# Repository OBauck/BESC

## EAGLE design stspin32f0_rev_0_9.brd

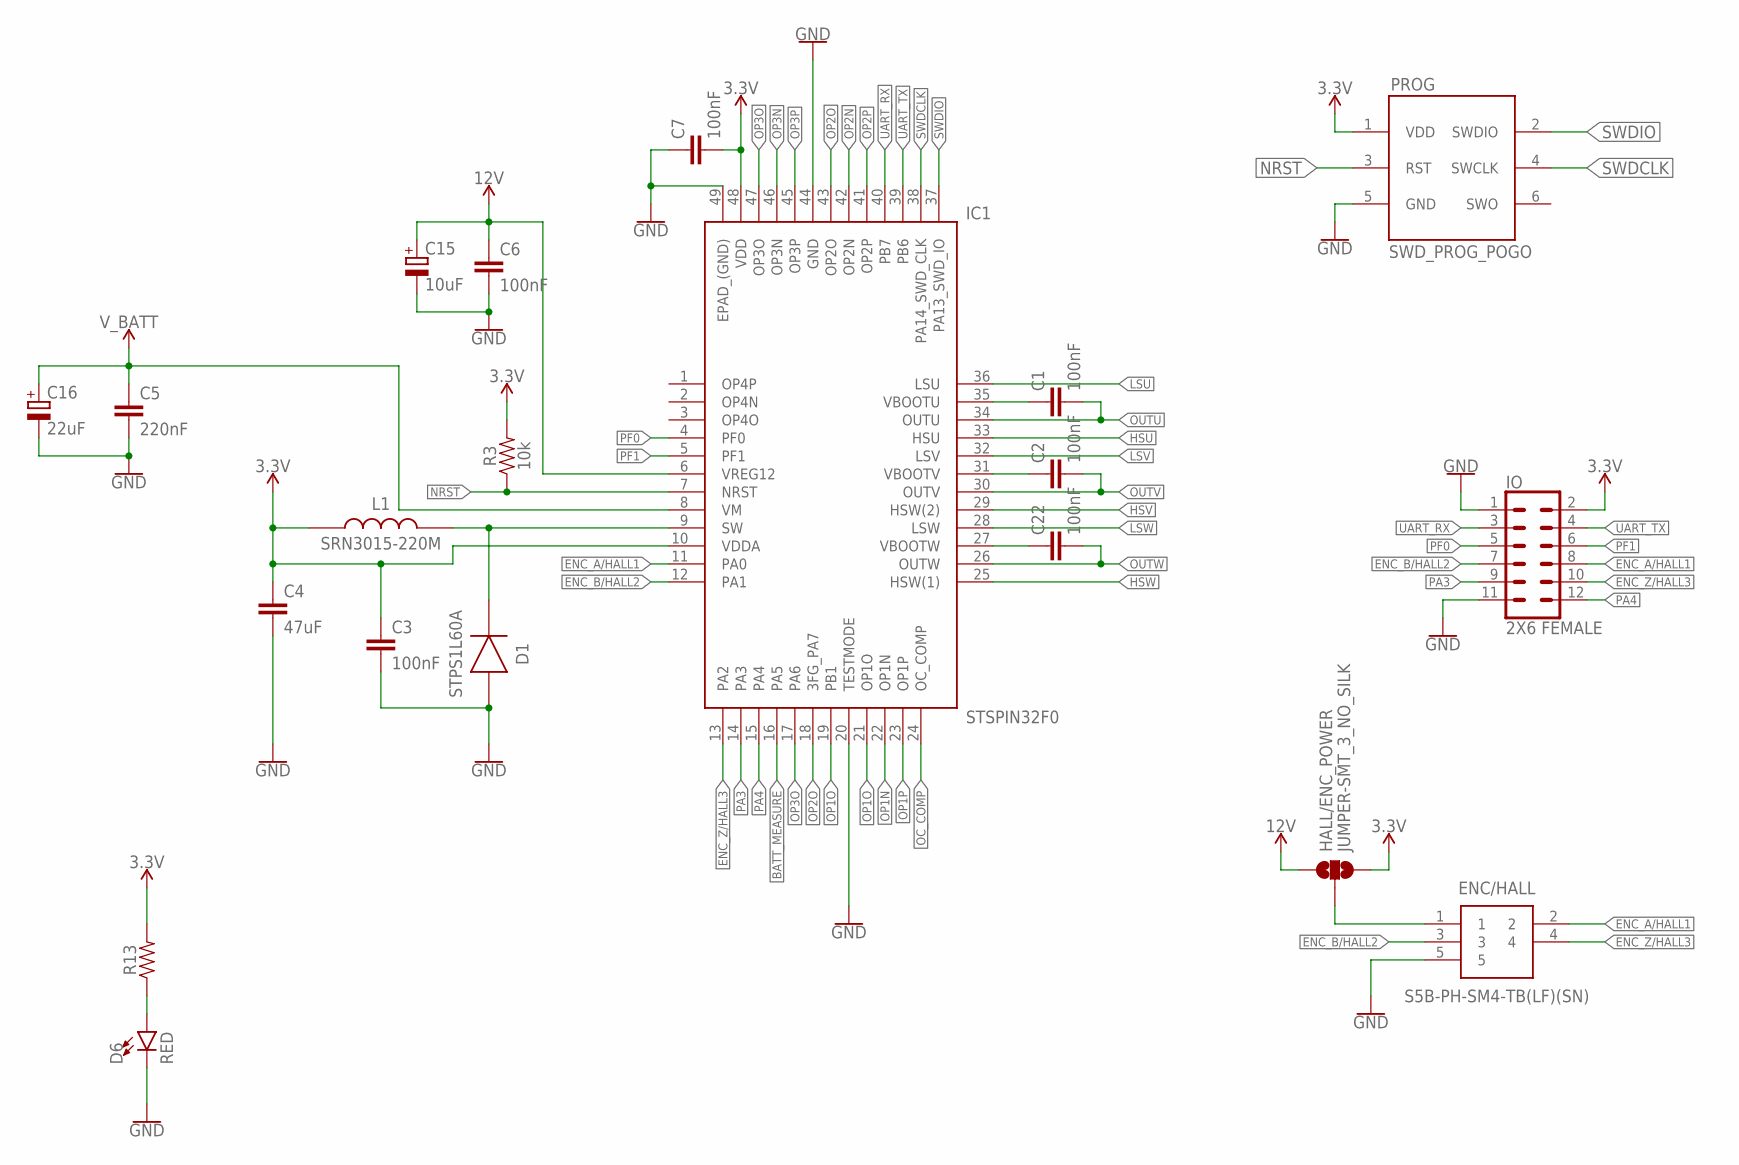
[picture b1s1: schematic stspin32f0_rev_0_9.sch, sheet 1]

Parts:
C1, C2, C3, C6, C7, C22: 100nF; 0603
C4: 47uF; 0805
C5: 220nF; 0805
C15: 10uF; UD-5X5,8_NICHICON
C16: 22uF; UD-6,3X5,8_NICHICON
D1: STPS1L60A; DIOM5126X265N
D6: RED; LED-0603
ENC/HALL: S5B-PH-SM4-TB(LF)(SN); S5B-PH-SM4-TB_1
HALL/ENC_POWER: JUMPER-SMT_3_NO_SILK; SMT-JUMPER_3_NO_SILK
IC1: STSPIN32F0; QFN50P700X700X100-49N
IO: 2X6 FEMALE; 2X6
L1: SRN3015-220M; SRN3015
PROG: SWD_PROG_POGO; 1X06_1.27MM
R3: 10k; 0603
R13: RES-1/10W-5%-0603; 0603

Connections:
3.3V: C3.1, C4.1, C7.2, HALL/ENC_POWER.3, IC1.10 (VDDA), IC1.48 (VDD), IO.2, L1.1, PROG.1 (VDD), R3.2, R13.2; also elsewhere on the board
12V: C6.1, C15.+, HALL/ENC_POWER.1, IC1.6 (VREG12)
BATT_MEASURE: IC1.16 (PA5); also elsewhere on the board
ENC_A/HALL1: ENC/HALL.2, IC1.11 (PA0), IO.8
ENC_B/HALL2: ENC/HALL.3, IC1.12 (PA1), IO.7
ENC_Z/HALL3: ENC/HALL.4, IC1.13 (PA2), IO.10
GND: C3.2, C4.2, C5.2, C6.2, C7.1, C15.-, C16.-, D1.2 (A), D6.C, ENC/HALL.5, IC1.20 (TESTMODE), IC1.44 (GND), IC1.49 (EPAD_(GND)), IO.1, IO.11, PROG.5 (GND); also elsewhere on the board
HSU: IC1.33 (HSU); also elsewhere on the board
HSV: IC1.29 (HSW(2)); also elsewhere on the board
HSW: IC1.25 (HSW(1)); also elsewhere on the board
LSU: IC1.36 (LSU); also elsewhere on the board
LSV: IC1.32 (LSV); also elsewhere on the board
LSW: IC1.28 (LSW); also elsewhere on the board
unnamed: C1.1, IC1.35 (VBOOTU)
unnamed: D1.1 (K), IC1.9 (SW), L1.2
unnamed: D6.A, R13.1
unnamed: C2.1, IC1.31 (VBOOTV)
unnamed: C22.1, IC1.27 (VBOOTW)
unnamed: ENC/HALL.1, HALL/ENC_POWER.2
NRST: IC1.7 (NRST), PROG.3 (RST), R3.1
OC_COMP: IC1.24 (OC_COMP); also elsewhere on the board
OP1N: IC1.22 (OP1N); also elsewhere on the board
OP1O: IC1.19 (PB1), IC1.21 (OP1O); also elsewhere on the board
OP1P: IC1.23 (OP1P); also elsewhere on the board
OP2N: IC1.42 (OP2N); also elsewhere on the board
OP2O: IC1.18 (3FG_PA7), IC1.43 (OP2O); also elsewhere on the board
OP2P: IC1.41 (OP2P); also elsewhere on the board
OP3N: IC1.46 (OP3N); also elsewhere on the board
OP3O: IC1.17 (PA6), IC1.47 (OP3O); also elsewhere on the board
OP3P: IC1.45 (OP3P); also elsewhere on the board
OUTU: C1.2, IC1.34 (OUTU); also elsewhere on the board
OUTV: C2.2, IC1.30 (OUTV); also elsewhere on the board
OUTW: C22.2, IC1.26 (OUTW); also elsewhere on the board
PA3: IC1.14 (PA3), IO.9
PA4: IC1.15 (PA4), IO.12
PF0: IC1.4 (PF0), IO.5
PF1: IC1.5 (PF1), IO.6
SWDCLK: IC1.38 (PA14_SWD_CLK), PROG.4 (SWCLK)
SWDIO: IC1.37 (PA13_SWD_IO), PROG.2 (SWDIO)
UART_RX: IC1.40 (PB7), IO.3
UART_TX: IC1.39 (PB6), IO.4
V_BATT: C5.1, C16.+, IC1.8 (VM); also elsewhere on the board

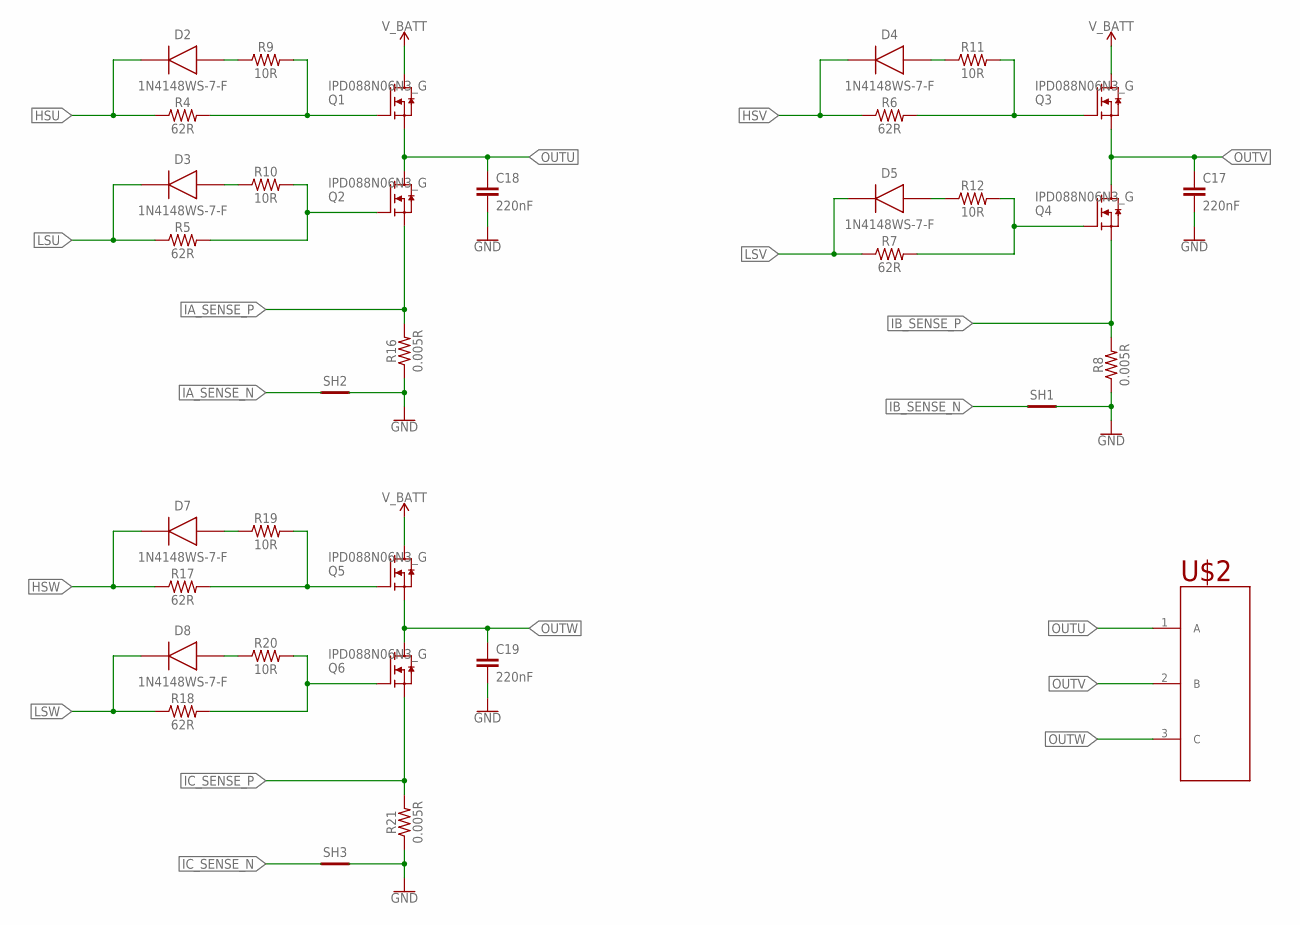
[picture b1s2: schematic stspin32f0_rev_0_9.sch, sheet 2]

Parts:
C17, C18, C19: 220nF; 0805
D2, D3, D4, D5, D7, D8: 1N4148WS-7-F; SOD2513X120N
Q1, Q2, Q3, Q4, Q5, Q6: IPD088N06N3_G; DPAK(TO-252-3)
R4, R5, R6, R7, R17, R18: 62R; 0603
R8, R16, R21: 0.005R; R2512
R9, R10, R11, R12, R19, R20: 10R; 0603
SH1, SH2, SH3: SHORTT5; SHORT_TOP-50
U$2: MR30; MR30PW

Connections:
GND: C17.2, C18.2, C19.2, R8.1, R16.1, R21.1, SH1.2, SH2.2, SH3.2; also elsewhere on the board
HSU: D2.1 (K), R4.1; also elsewhere on the board
HSV: D4.1 (K), R6.1; also elsewhere on the board
HSW: D7.1 (K), R17.1; also elsewhere on the board
IA_SENSE_N: SH2.1; also elsewhere on the board
IA_SENSE_P: Q2.3 (S), R16.2; also elsewhere on the board
IB_SENSE_N: SH1.1; also elsewhere on the board
IB_SENSE_P: Q4.3 (S), R8.2; also elsewhere on the board
IC_SENSE_N: SH3.1; also elsewhere on the board
IC_SENSE_P: Q6.3 (S), R21.2; also elsewhere on the board
LSU: D3.1 (K), R5.1; also elsewhere on the board
LSV: D5.1 (K), R7.1; also elsewhere on the board
LSW: D8.1 (K), R18.1; also elsewhere on the board
unnamed: D7.2 (A), R19.1
unnamed: D8.2 (A), R20.1
unnamed: D4.2 (A), R11.1
unnamed: D2.2 (A), R9.1
unnamed: D3.2 (A), R10.1
unnamed: Q6.1 (G), R18.2, R20.2
unnamed: D5.2 (A), R12.1
unnamed: Q5.1 (G), R17.2, R19.2
unnamed: Q4.1 (G), R7.2, R12.2
unnamed: Q3.1 (G), R6.2, R11.2
unnamed: Q2.1 (G), R5.2, R10.2
unnamed: Q1.1 (G), R4.2, R9.2
OUTU: C18.1, Q1.3 (S), Q2.2 (D), U$2.1 (A); also elsewhere on the board
OUTV: C17.1, Q3.3 (S), Q4.2 (D), U$2.2 (B); also elsewhere on the board
OUTW: C19.1, Q5.3 (S), Q6.2 (D), U$2.3 (C); also elsewhere on the board
V_BATT: Q1.2 (D), Q3.2 (D), Q5.2 (D); also elsewhere on the board

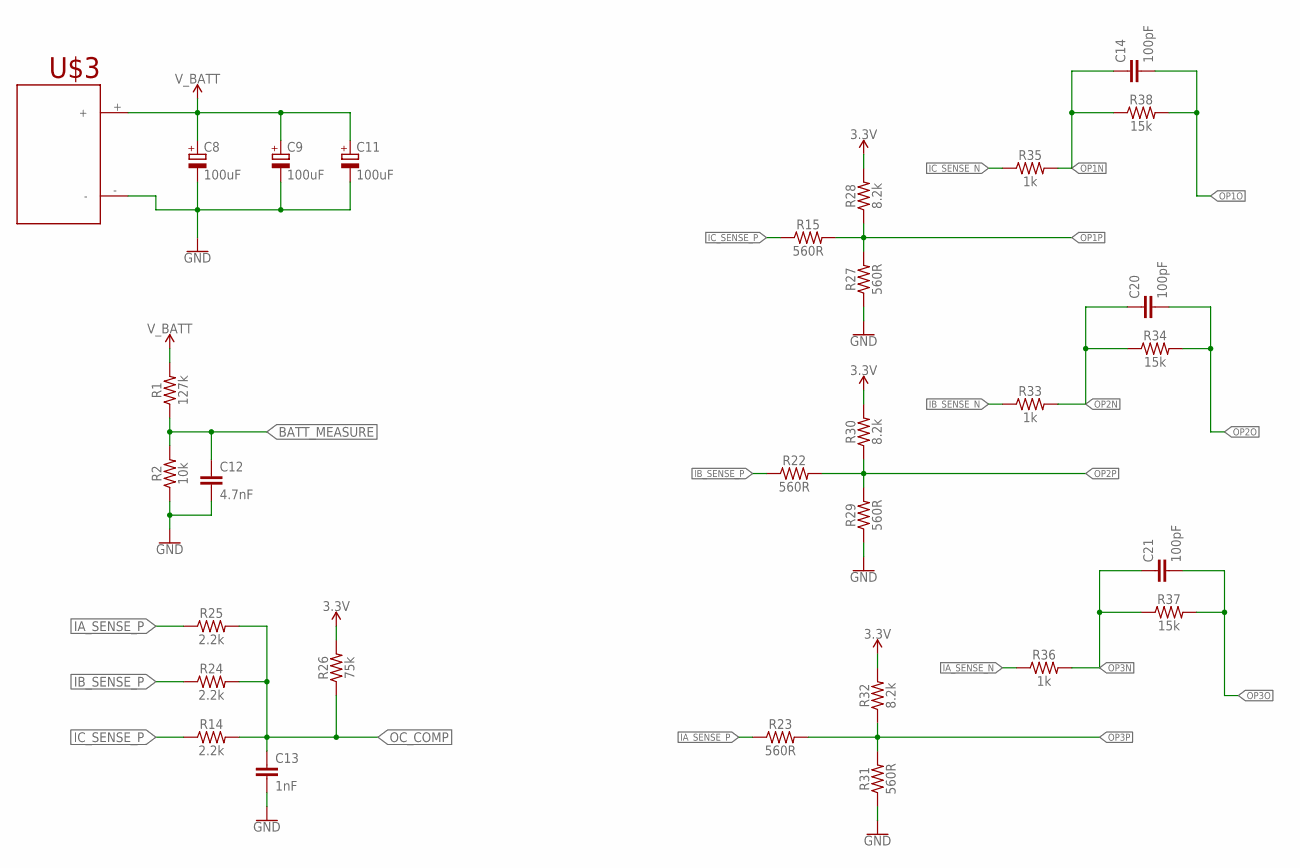
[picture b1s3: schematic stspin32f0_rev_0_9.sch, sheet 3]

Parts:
C8, C9, C11: 100uF; UD-6,3X7,7_NICHICON
C12: 4.7nF; 0603
C13: 1nF; 0603
C14, C20, C21: 100pF; 0603
R1: 127k; 0603
R2: 10k; 0603
R14, R24, R25: 2.2k; 0603
R15, R22, R23, R27, R29, R31: 560R; 0603
R26: 75k; 0603
R28, R30, R32: 8.2k; 0603
R33, R35, R36: 1k; 0603
R34, R37, R38: 15k; 0603
U$3: XT30; XT30PW

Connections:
3.3V: R26.2, R28.2, R30.2, R32.2; also elsewhere on the board
BATT_MEASURE: C12.1, R1.1, R2.2; also elsewhere on the board
GND: C8.-, C9.-, C11.-, C12.2, C13.2, R2.1, R27.1, R29.1, R31.1, U$3.-; also elsewhere on the board
IA_SENSE_N: R36.1; also elsewhere on the board
IA_SENSE_P: R23.1, R25.1; also elsewhere on the board
IB_SENSE_N: R33.1; also elsewhere on the board
IB_SENSE_P: R22.1, R24.1; also elsewhere on the board
IC_SENSE_N: R35.1; also elsewhere on the board
IC_SENSE_P: R14.1, R15.1; also elsewhere on the board
OC_COMP: C13.1, R14.2, R24.2, R25.2, R26.1; also elsewhere on the board
OP1N: C14.1, R35.2, R38.1; also elsewhere on the board
OP1O: C14.2, R38.2; also elsewhere on the board
OP1P: R15.2, R27.2, R28.1; also elsewhere on the board
OP2N: C20.1, R33.2, R34.1; also elsewhere on the board
OP2O: C20.2, R34.2; also elsewhere on the board
OP2P: R22.2, R29.2, R30.1; also elsewhere on the board
OP3N: C21.1, R36.2, R37.1; also elsewhere on the board
OP3O: C21.2, R37.2; also elsewhere on the board
OP3P: R23.2, R31.2, R32.1; also elsewhere on the board
V_BATT: C8.+, C9.+, C11.+, R1.2, U$3.+; also elsewhere on the board

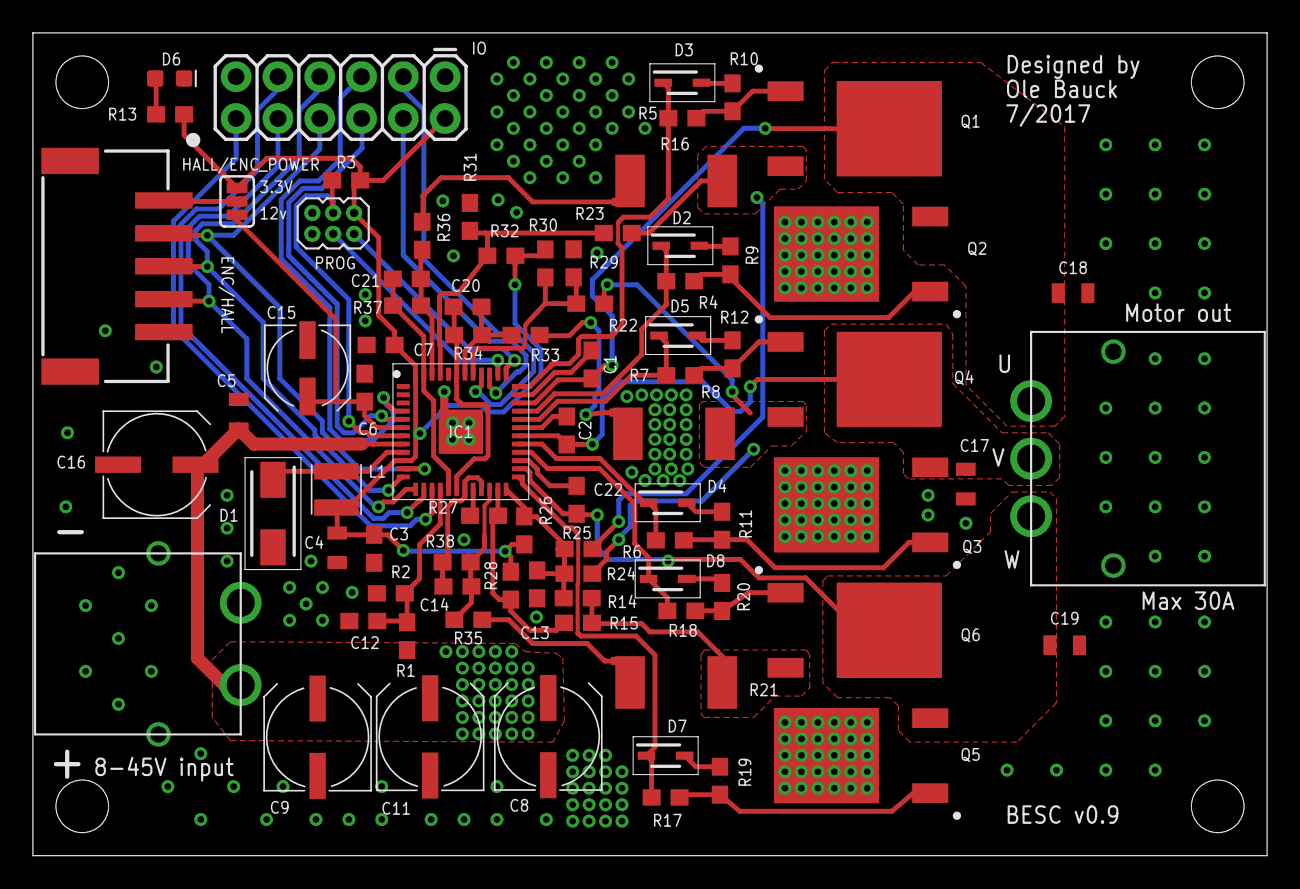
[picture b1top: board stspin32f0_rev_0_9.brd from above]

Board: 2 copper layers, 75.0 x 50.0 mm, 84 parts (0 on the bottom side), 60 nets.

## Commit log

2017-07-10 first commit, board almost routed
2017-07-10 routing done and drc cleared
2017-07-10 added gerber files
2017-07-10 minor fixes
2017-07-10 fixed names
2017-07-14 More vias and wider tracks for more current
2017-07-15 gerbers for first revision ordered

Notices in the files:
parts and their libraries:
SparkFun-LED: Licensing: Creative Commons ShareAlike 4.0 International - https://creativecommons.org/licenses/by-sa/4.0
